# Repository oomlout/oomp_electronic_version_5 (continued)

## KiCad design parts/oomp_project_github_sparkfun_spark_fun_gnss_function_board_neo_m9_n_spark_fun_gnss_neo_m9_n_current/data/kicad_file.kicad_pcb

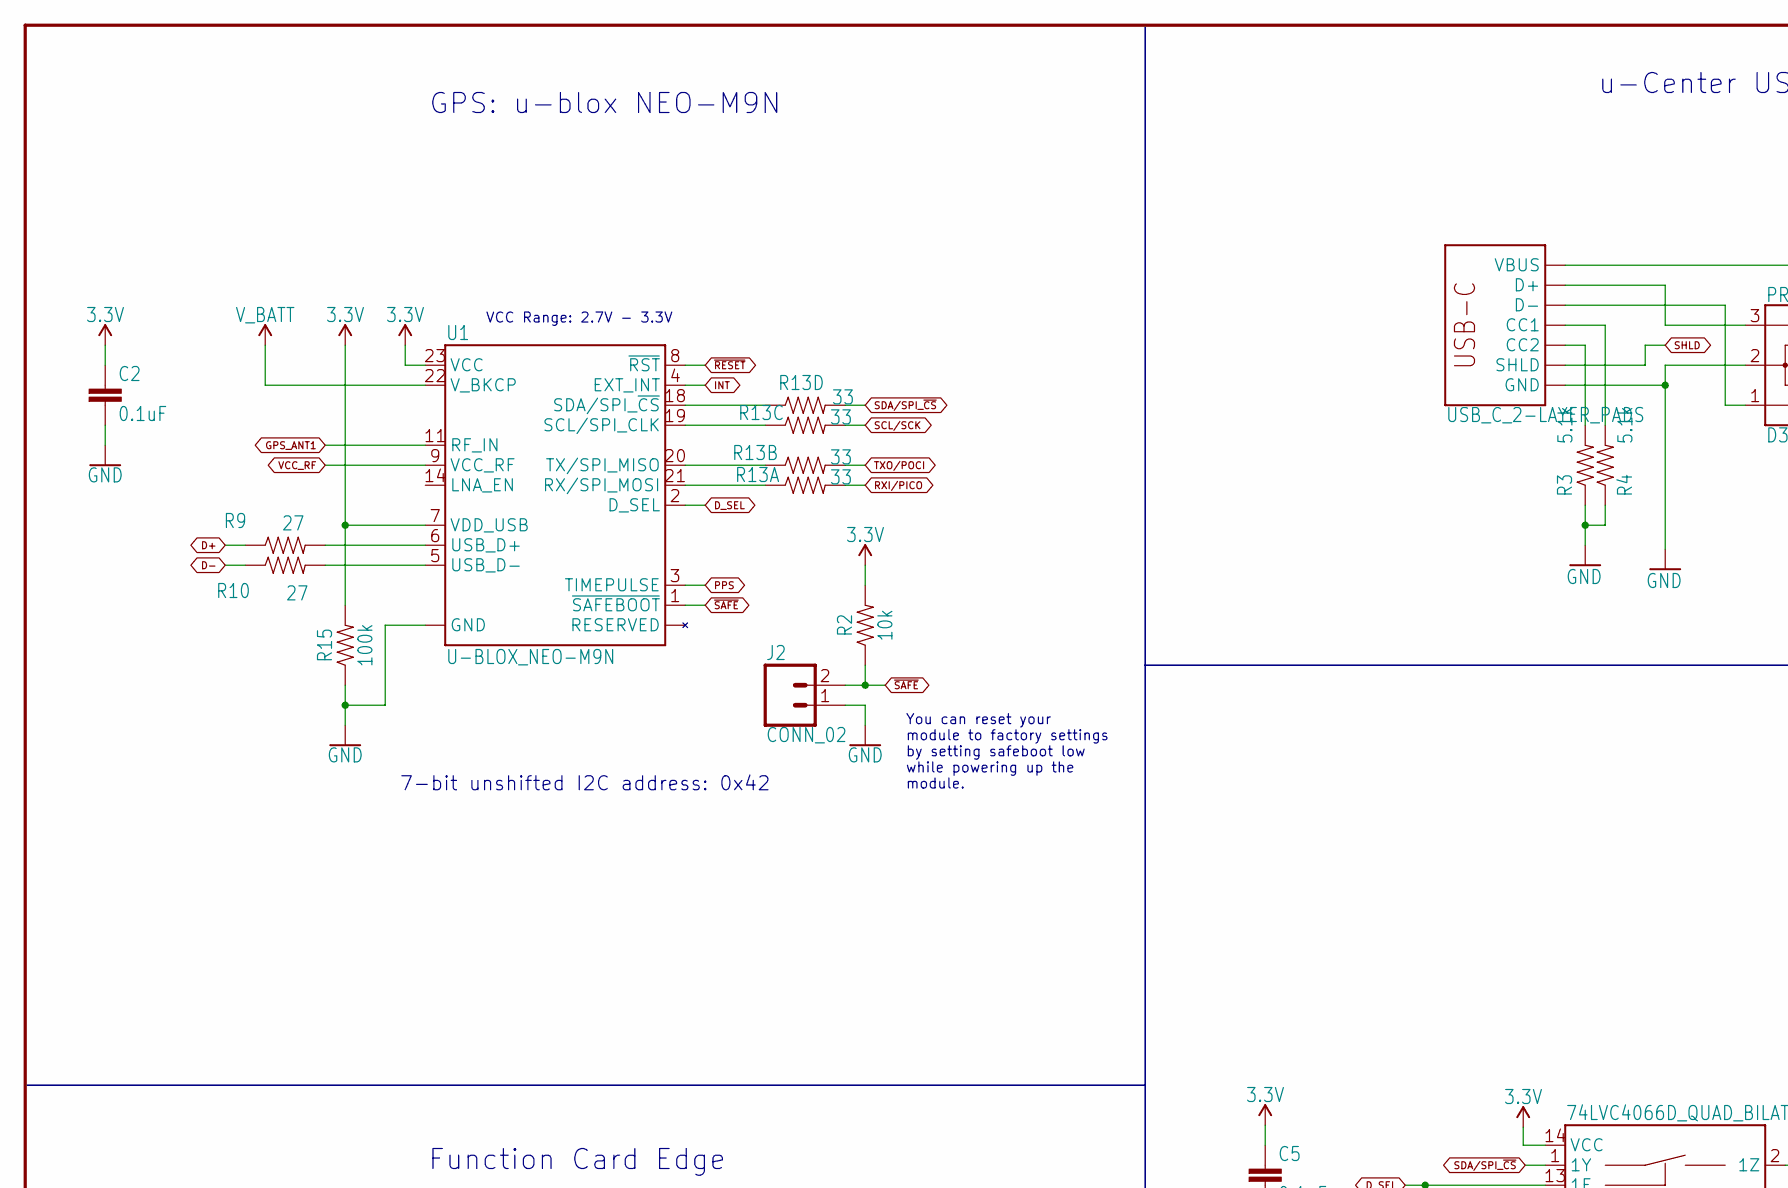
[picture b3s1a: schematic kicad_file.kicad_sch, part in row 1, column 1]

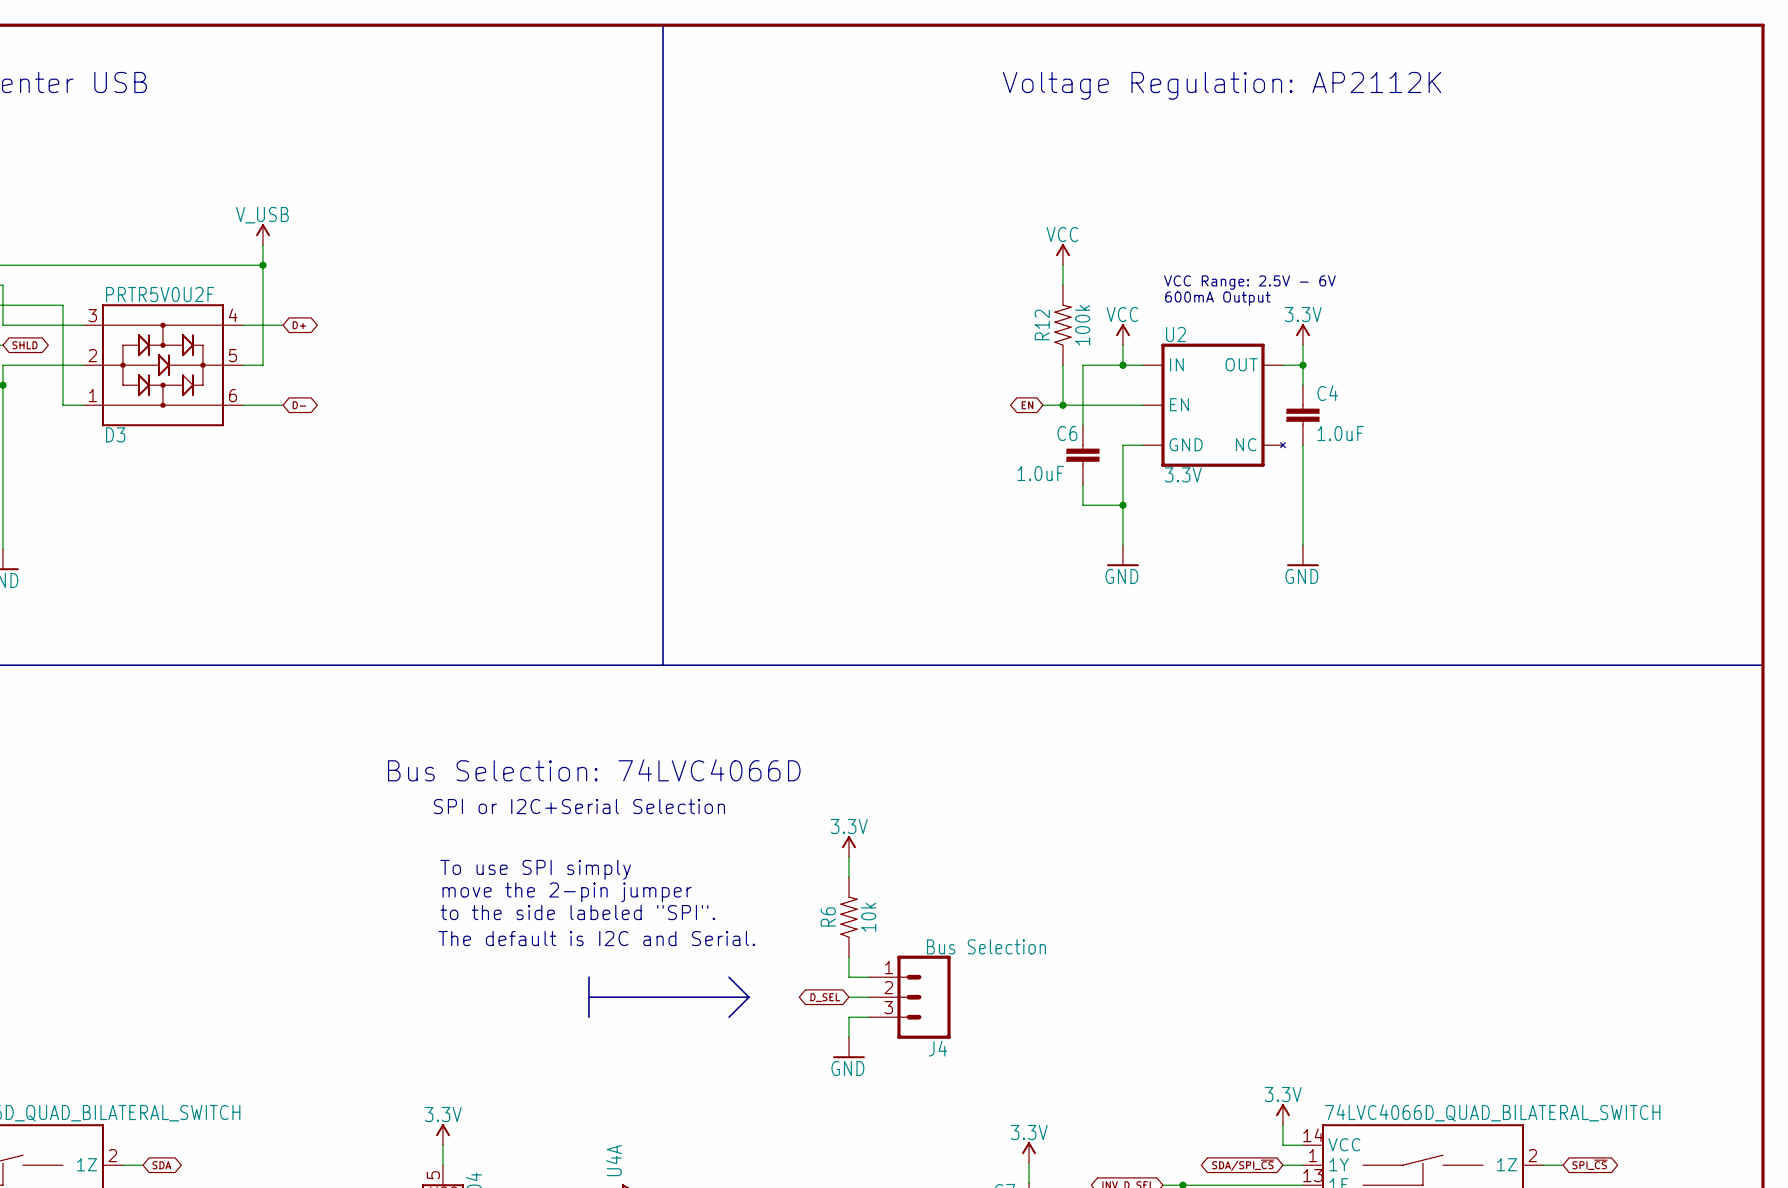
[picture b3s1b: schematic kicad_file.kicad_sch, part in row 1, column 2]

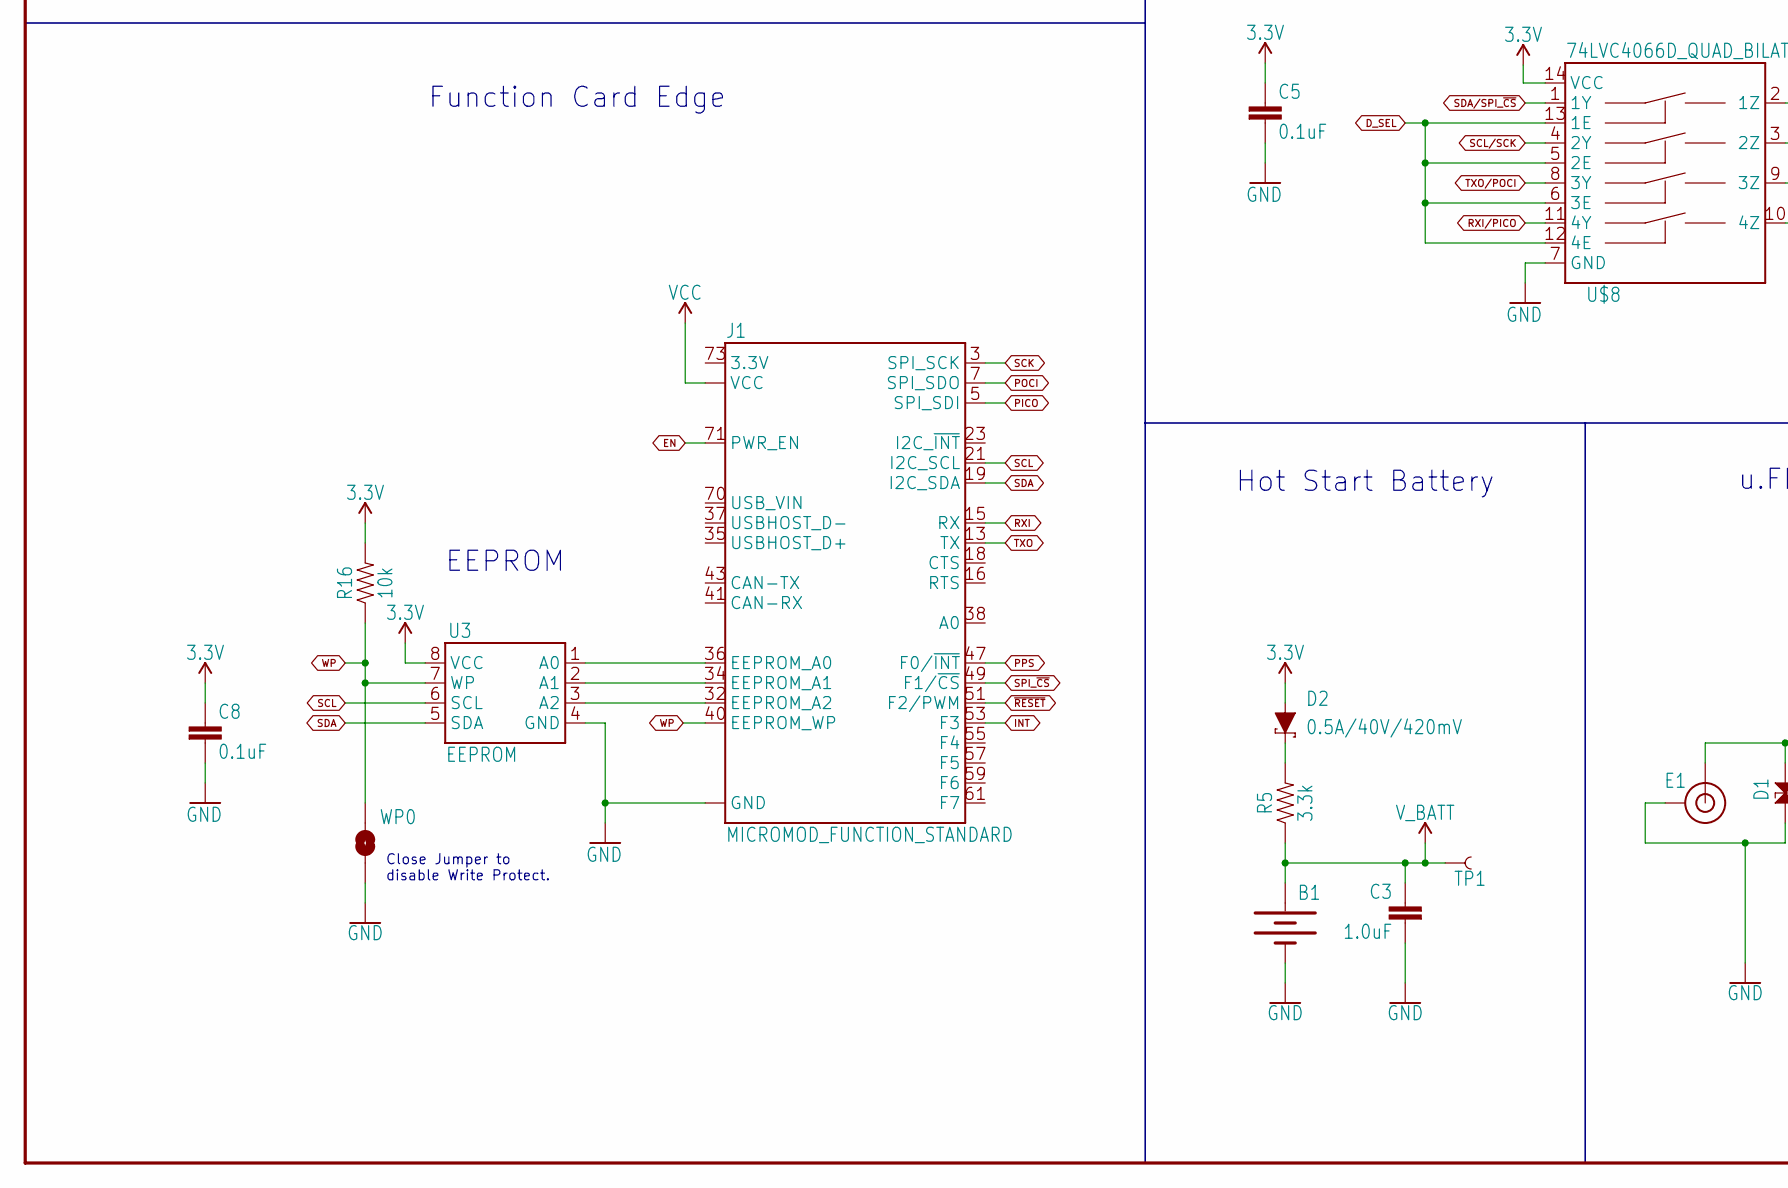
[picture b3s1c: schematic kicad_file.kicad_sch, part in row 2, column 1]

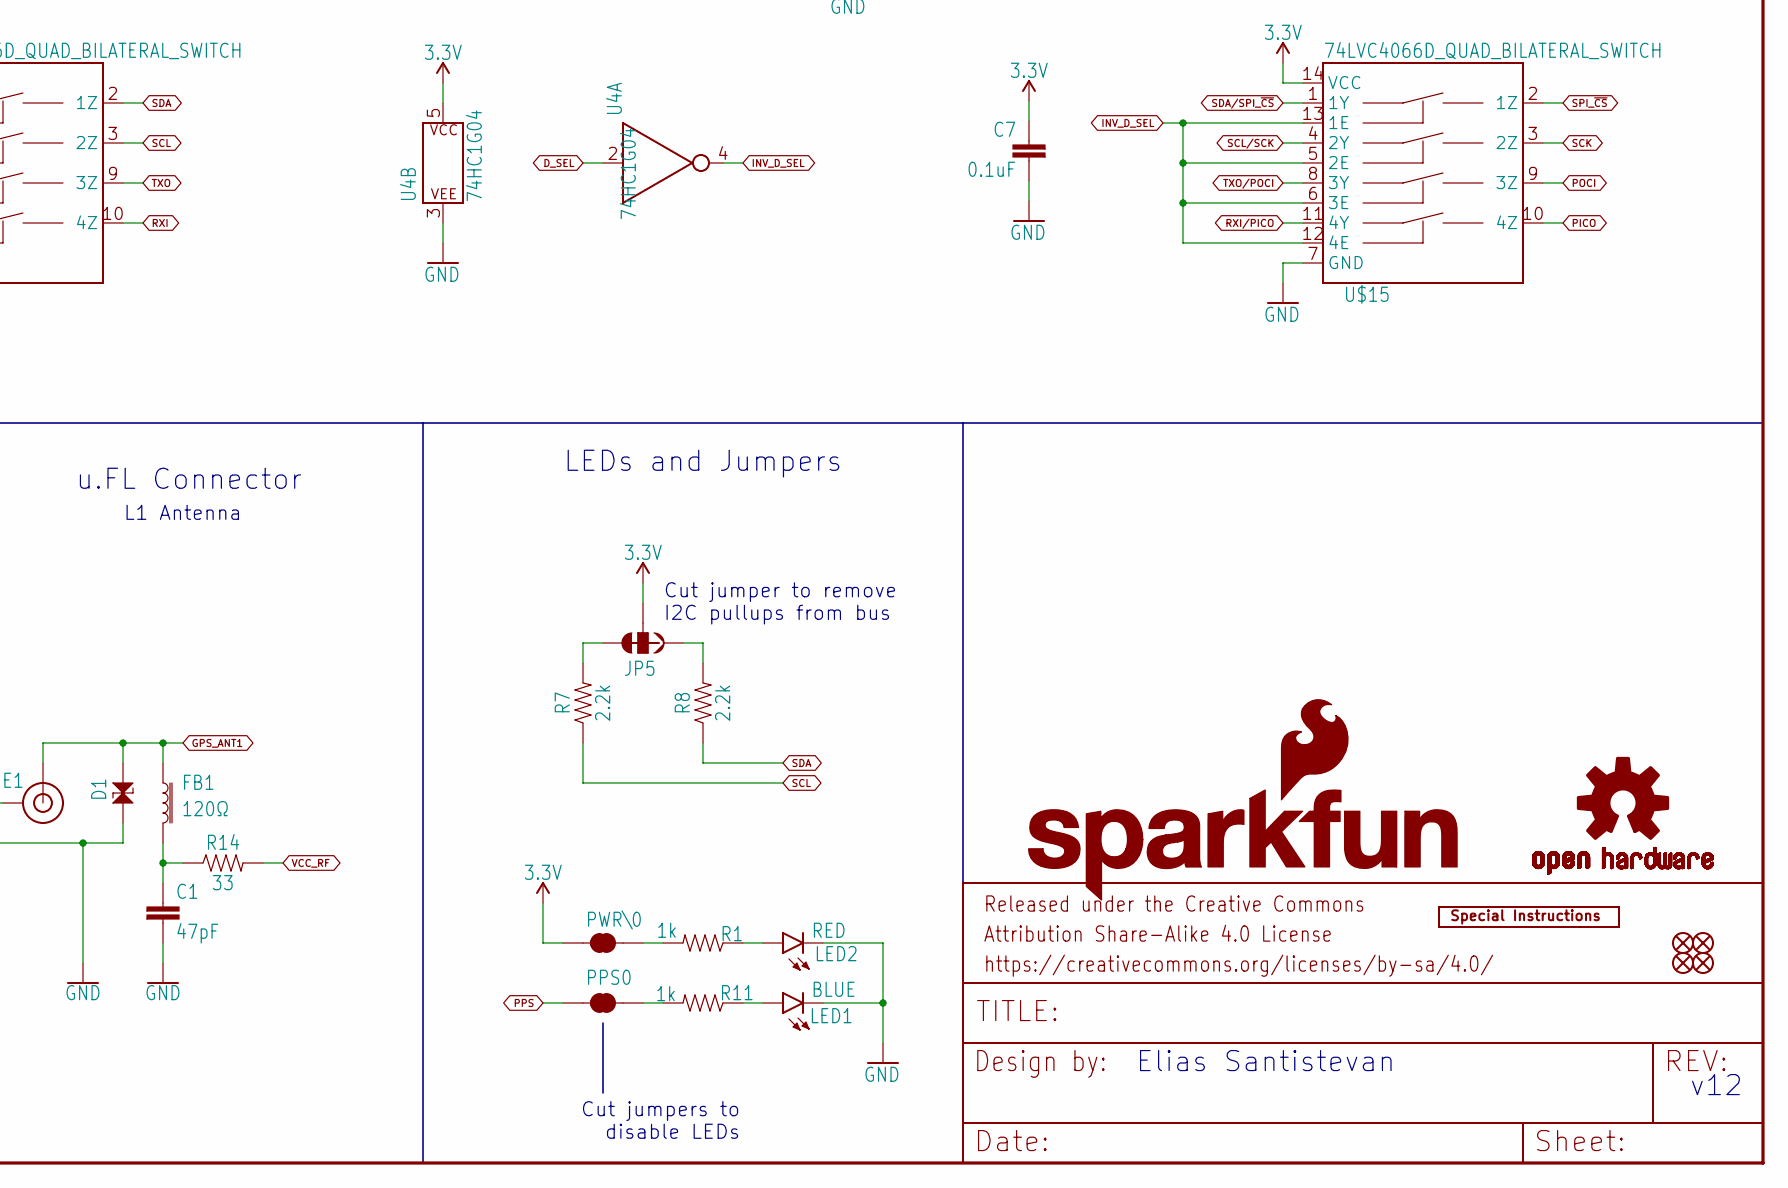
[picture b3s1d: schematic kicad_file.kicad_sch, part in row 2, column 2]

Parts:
B1: 6.8MM_COIN_CELL; MS421R_IV03E
C1: 47pF; 0402
C2: 0.1uF; 0402-TIGHT
C3, C4, C6: 1.0uF; 0603
C5, C7, C8: 0.1uF; 0603
D1: PESD0402-0402T; 0402-TIGHT
D2: 0.5A/40V/420mV; SOD-323
D3: PRTR5V0U2F; SOT886
E1: U.FL
FB1: 120Ω; 0402; MFG_PART BLM15HB121SN1D
FD1, FD2, FD3, FD4: FIDUCIAL1X2; FIDUCIAL-1X2
FRAME2: FRAME-LEDGER; CREATIVE_COMMONS
J1: MICROMOD_FUNCTION_STANDARD; M.2-CARD-E-22_FUNCTION_STANDARD
J2: CONN_02; 1X02
J3: USB_C_2-LAYER_PADS; USB-C-16P-2LAYER-PADS
J4: Bus Selection; 1X03_LOCK
JP5: JUMPER-SMT_3_2-NC_TRACE_SILK; SMT-JUMPER_3_2-NC_TRACE_SILK
LED1: BLUE; LED-0603
LED2: RED; LED-0603
LOGO1: SPECIAL_INSTRUCTIONS-ORDERING; ORDERING_INSTRUCTIONS
LOGO2: SFE_LOGO_NAME_FLAME.2_INCH; SFE_LOGO_NAME_FLAME_.2
LOGO3: OSHW-LOGOS; OSHW-LOGO-S
PPS0: JUMPER-SMT_2_NC_TRACE_SILK; SMT-JUMPER_2_NC_TRACE_SILK
PWR\0: JUMPER-SMT_2_NC_TRACE_SILK; SMT-JUMPER_2_NC_TRACE_SILK
R1, R11: 1k; 0603
R2, R6, R16: 10k; 0603
R3, R4: 5.1k; 0603
R5: 3.3k; 0603
R7, R8: 2.2k; 0603
R9, R10: 27; 0603
R12, R15: 100k; 0603
R13: 33; 1206_RA
R14: 33; 0402
TP1: TEST-POINT3X4; PAD.03X.04
U1: U-BLOX_NEO-M9N; NEO-M9N_M8T_M8U_D9S
U2: 3.3V; SOT23-5
U3: EEPROM; SO08
U4: 74HC1G04; SOT353
U$8, U$15: 74LVC4066D_QUAD_BILATERAL_SWITCH; SO14
WP0: JUMPER-SMT_2_NO_SILK; SMT-JUMPER_2_NO_SILK

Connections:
3.3V: C2.1, C4.1, C5.1, C7.1, C8.1, D2.A, JP5.2, PWR\0.2, R2.2, R6.2, R15.2, R16.2, U1.7 (VDD_USB), U1.23 (VCC), U2.5 (OUT), U3.8 (VCC), U4.5 (P$V+), U$8.14 (VCC), U$15.14 (VCC)
A0: J1.36 (EEPROM_A0), U3.1 (A0)
A1: J1.34 (EEPROM_A1), U3.2 (A1)
A2: J1.32 (EEPROM_A2), U3.3 (A2)
D+: D3.4, R9.1
D-: D3.6, R10.1
D_SEL: J4.2, U1.2 (D_SEL), U4.2 (A), U$8.5 (2E), U$8.6 (3E), U$8.12 (4E), U$8.13 (1E)
EN: J1.71 (PWR_EN), R12.1, U2.3 (EN)
GND: B1.-, C1.2, C2.2, C3.2, C4.2, C5.2, C6.2, C7.2, C8.2, D1.1, D3.2, E1.1 (GND), E1.2 (GND), J1.1 (GND), J1.33 (GND), J1.39 (GND), J1.45 (GND), J1.75 (GND), J1.GND1 (GND), J1.GND2 (GND), J1.GND3 (GND), J1.GND4 (GND), J1.GND5 (GND), J1.GND6 (GND), J2.1, J3.GND, J3.GND2 (GND), J4.3, LED1.C, LED2.C, R3.1, R4.1, R15.1, U1.10 (GND), U1.12 (GND), U1.13 (GND), U1.24 (GND), U2.2 (GND), U3.4 (GND), U4.3 (P$V-), U$8.7 (GND), U$15.7 (GND), WP0.1
GPS_ANT1: D1.2, E1.FEED (SIGNAL), FB1.1, U1.11 (RF_IN)
INT: J1.53 (F3), U1.4 (EXT_INT)
INV_D_SEL: U4.4 (Y), U$15.5 (2E), U$15.6 (3E), U$15.12 (4E), U$15.13 (1E)
unnamed: PWR\0.1, R1.2
unnamed: LED1.A, R11.1
unnamed: C1.1, FB1.2, R14.1
unnamed: PPS0.1, R11.2
unnamed: JP5.1, R8.2
unnamed: D2.C, R5.2
unnamed: J3.A5 (CC1), R4.2
unnamed: JP5.3, R7.2
unnamed: J3.B5 (CC2), R3.2
unnamed: LED2.A, R1.1
unnamed: R9.2, U1.6 (USB_D+)
unnamed: R10.2, U1.5 (USB_D-)
unnamed: J4.1, R6.1
PICO: J1.5 (SPI_SDI), U$15.10 (4Z)
POCI: J1.7 (SPI_SDO), U$15.9 (3Z)
PPS: J1.47 (F0/~INT), PPS0.2, U1.3 (TIMEPULSE)
RXI: J1.15 (RX), U$8.10 (4Z)
RXI/PICO: R13.P8 (2), U$8.11 (4Y), U$15.11 (4Y)
RXLV: R13.P1 (1), U1.21 (RX/SPI_MOSI)
SCK: J1.3 (SPI_SCK), U$15.3 (2Z)
SCL: J1.21 (I2C_SCL), R7.1, U3.6 (SCL), U$8.3 (2Z)
SCL/SCK: R13.P6 (2), U$8.4 (2Y), U$15.4 (2Y)
SCL_LV: R13.P3 (1), U1.19 (SCL/SPI_CLK)
SDA: J1.19 (I2C_SDA), R8.1, U3.5 (SDA), U$8.2 (1Z)
SDA/SPI_~CS: R13.P5 (2), U$8.1 (1Y), U$15.1 (1Y)
SDA_LV: R13.P4 (1), U1.18 (SDA/SPI_~CS)
SHLD: J3.SHLD1 (SHLD), J3.SHLD2 (SHLD), J3.SHLD3 (SHLD), J3.SHLD4 (SHLD)
SPI_~CS: J1.49 (F1/~CS), U$15.2 (1Z)
TXLV: R13.P2 (1), U1.20 (TX/SPI_MISO)
TXO: J1.13 (TX), U$8.9 (3Z)
TXO/POCI: R13.P7 (2), U$8.8 (3Y), U$15.8 (3Y)
USB_D+: D3.3, J3.A6 (D+), J3.B6 (D+)
USB_D-: D3.1, J3.A7 (D-), J3.B7 (D-)
VCC: C6.1, J1.72 (VCC), J1.74 (VCC), R12.2, U2.1 (IN)
VCC_RF: R14.2, U1.9 (VCC_RF)
V_BATT: B1.+, C3.1, R5.1, TP1.1, U1.22 (V_BKCP)
V_USB: D3.5, J3.VBUS1 (VBUS), J3.VBUS2 (VBUS)
WP: J1.40 (EEPROM_WP), R16.1, U3.7 (WP), WP0.2
~RESET: J1.51 (F2/PWM), U1.8 (~RST)
~SAFE: J2.2, R2.1, U1.1 (~SAFEBOOT)

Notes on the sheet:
LEDs and Jumpers
Function Card Edge
Elias Santistevan
Voltage Regulation: AP2112K
VCC Range: 2.7V - 3.3V
Cut jumper to remove I2C pullups from bus
7-bit unshifted I2C address: 0x42
GPS: u-blox NEO-M9N
EEPROM
To use SPI simply move the 2-pin jumper to the side labeled "SPI".
SPI or I2C+Serial Selection
L1 Antenna
Cut jumpers to disable LEDs
v12
u-Center USB
The default is I2C and Serial.
Close Jumper to disable Write Protect.
Bus Selection: 74LVC4066D
VCC Range: 2.5V - 6V 600mA Output
Hot Start Battery
u.FL Connector
You can reset your module to factory settings by setting safeboot low while powering up the module.

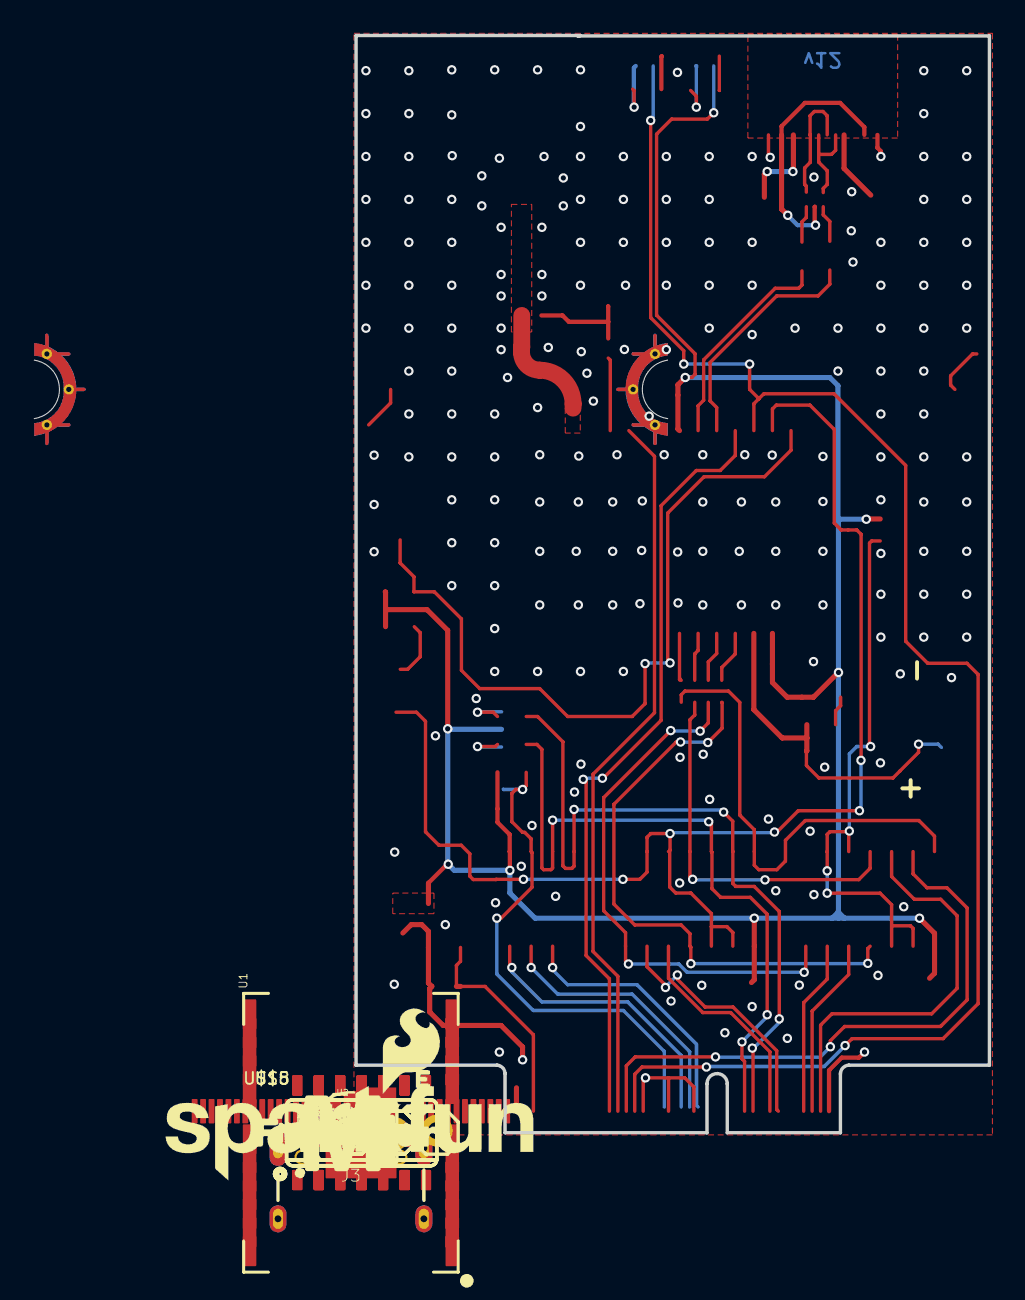
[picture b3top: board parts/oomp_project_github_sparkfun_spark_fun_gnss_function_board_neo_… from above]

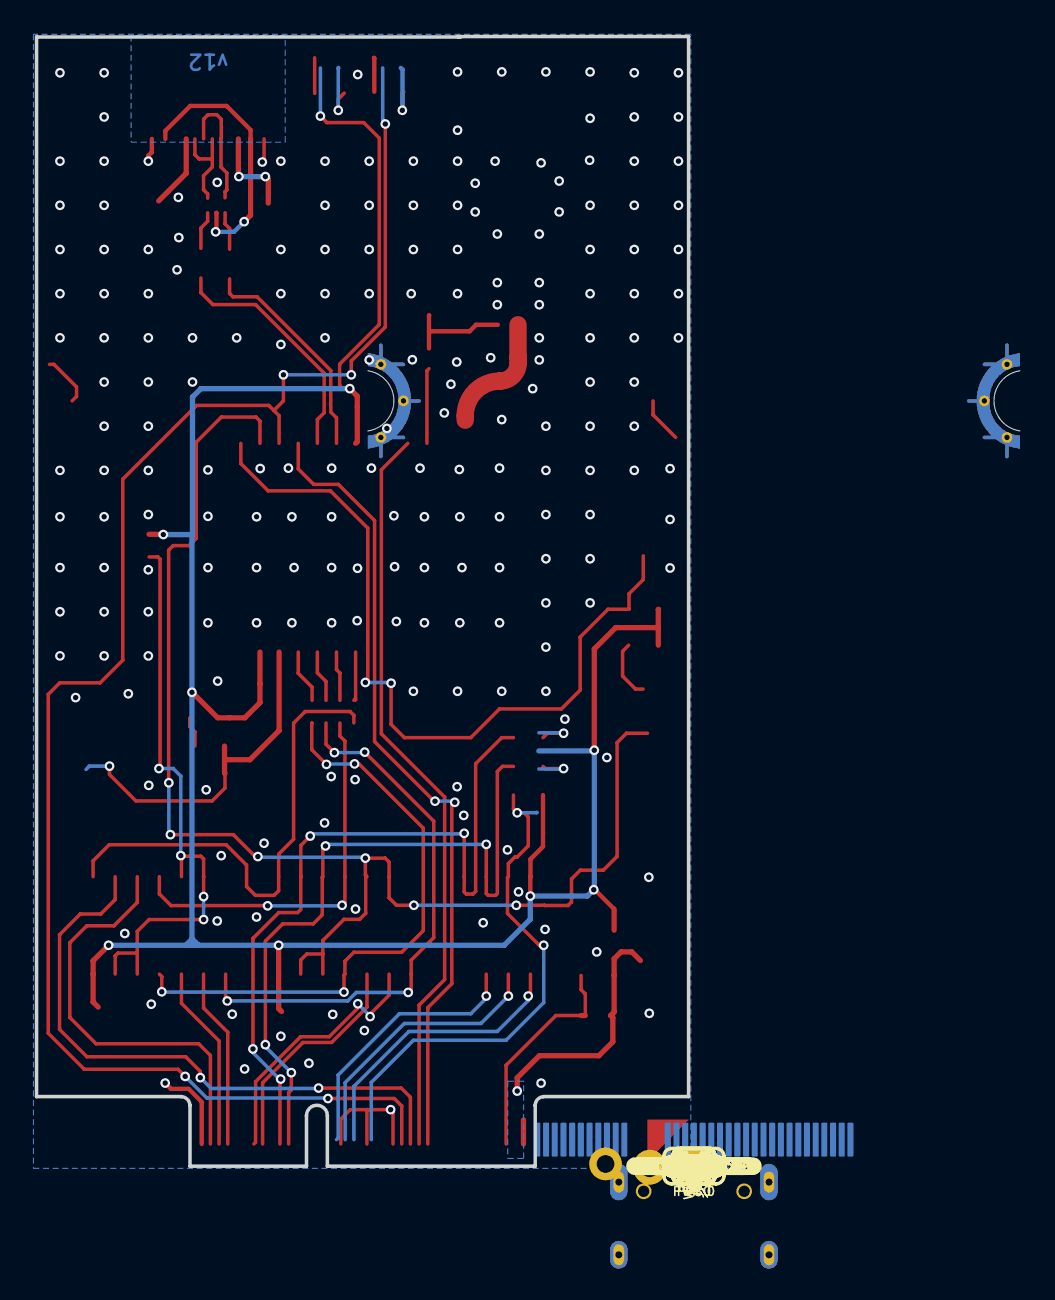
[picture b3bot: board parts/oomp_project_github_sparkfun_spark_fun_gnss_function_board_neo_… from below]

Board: 2 copper layers, 37.5 x 64.9 mm, 79 parts (17 on the bottom side), 52 nets.

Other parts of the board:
U$1: 3V313
U$2: PPS13
U$3: FUNCTION521
U$4, U$23: ##SAFEBOOT##882188213
U$5: U#BLOX11
U$6: NEO#M9N12
U$7: ANTENNA14
U$9: U#CENTER15
U$10: #I2C#18
U$11: MICROMOD_MI_LOGO_1
U$12: #3V3_LED#403132222514
U$13: #PPS_LED#403132222514
U$14: L1321542
U$16, U$24: #SPI#40313521
U$17, U$26: #SERIAL#I2C#40313523
U$18, U$22: #BUS_SELECT#509
U$19, U$25: #DSEL#40313522
U$20: #WP#13215403132222564
U$21: GNSS2222502

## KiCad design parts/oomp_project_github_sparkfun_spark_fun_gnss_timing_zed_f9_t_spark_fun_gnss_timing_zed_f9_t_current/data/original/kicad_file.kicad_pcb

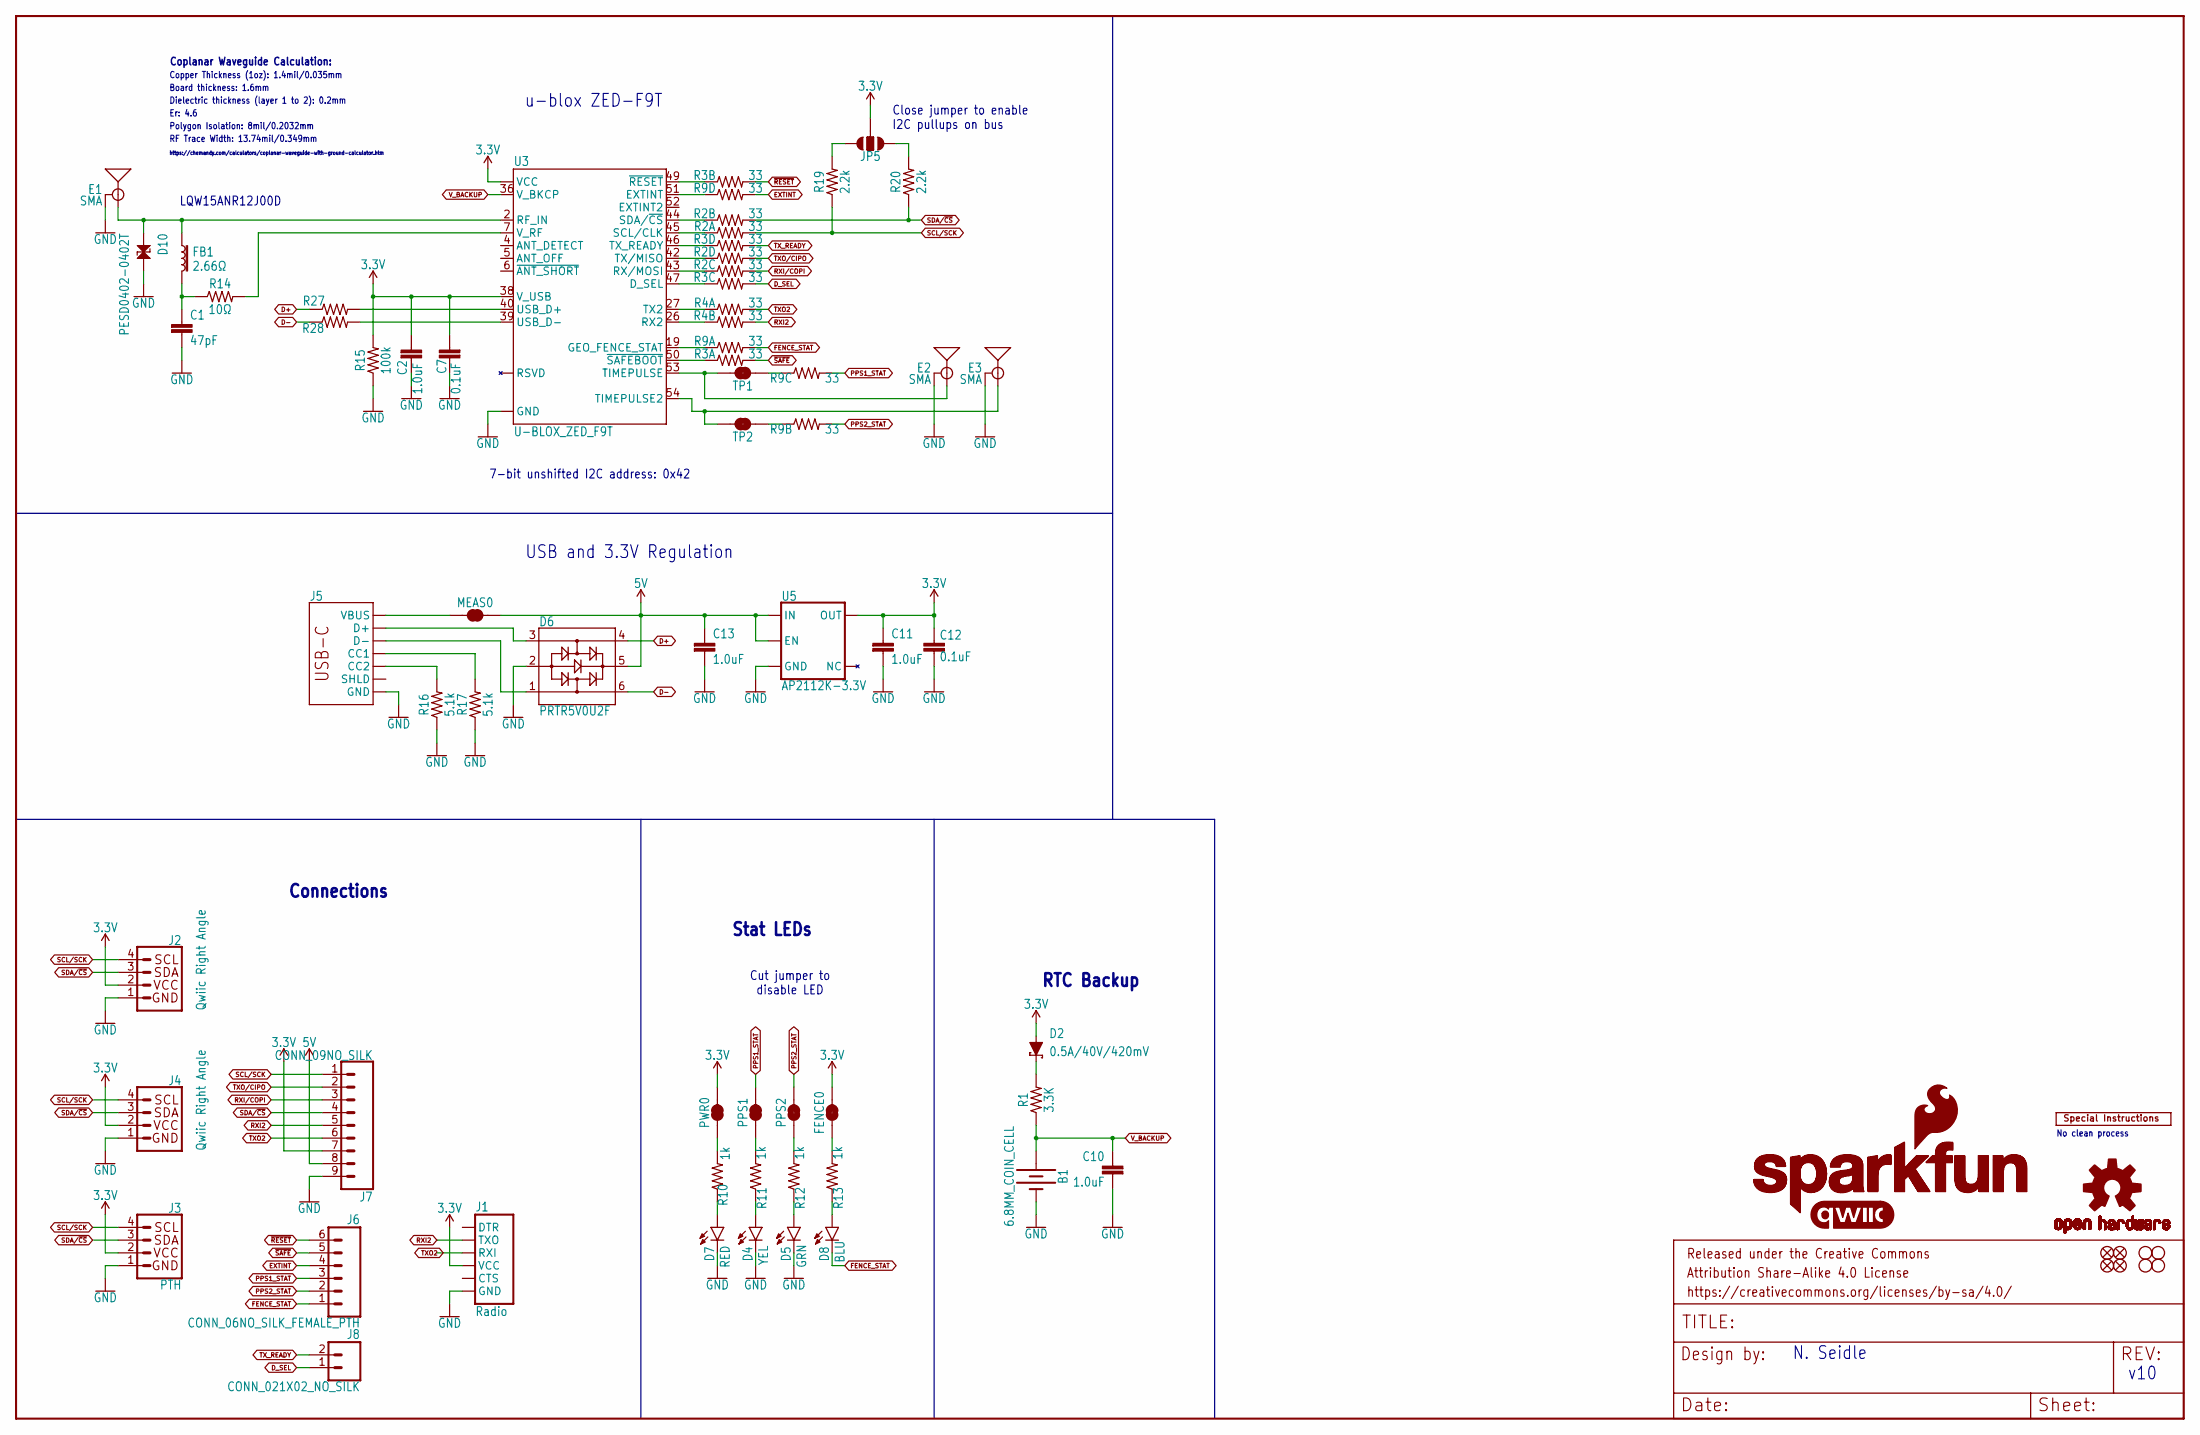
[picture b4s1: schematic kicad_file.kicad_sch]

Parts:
B1: 6.8MM_COIN_CELL; ML414H_IV01E
C1: 47pF; 0402-TIGHT
C2, C10, C11, C13: 1.0uF; 0402-TIGHT
C7, C12: 0.1uF; 0402-TIGHT
D2: 0.5A/40V/420mV; SOD-323
D4: YEL; LED-0603
D5: GRN; LED-0603
D6: PRTR5V0U2F; SOT886
D7: RED; LED-0603
D8: BLU; LED-0603
D10: PESD0402-0402T; 0402-TIGHT
E1, E2, E3: SMA; SMA-EDGE
FB1: 2.66Ω; 0402-TIGHT
FENCE0: JUMPER-SMT_2_NC_TRACE_SILK; SMT-JUMPER_2_NC_TRACE_SILK
FRAME2: FRAME-LEDGER; CREATIVE_COMMONS
H1, H2, H3, H4: STAND-OFF
J1: Radio; 1X06_NO_SILK
J2, J4: Qwiic Right Angle; JST04_1MM_RA
J3: PTH; 1X04_NO_SILK
J5: USB Female Type C Connector; USB-C-16P_4LAYER-PADS
J6: CONN_06NO_SILK_FEMALE_PTH; 1X06_NO_SILK
J7: CONN_09NO_SILK; 1X09_NO_SILK
J8: CONN_021X02_NO_SILK; 1X02_NO_SILK
JP5: JUMPER-SMT_3_NO_SILK; SMT-JUMPER_3_NO_SILK
JP21, JP61, JP71, JP81: FIDUCIALUFIDUCIAL; FIDUCIAL-MICRO
LOGO1: OSHW-LOGOMINI; OSHW-LOGO-MINI
LOGO2: SFE_LOGO_NAME_FLAME.1_INCH; SFE_LOGO_NAME_FLAME_.1
LOGO4: QWIIC_LOGO_4MM; QWIIC_4MM
LOGO5: SFE_LOGO_NAME.1_INCH; SFE_LOGO_NAME_.1
MEAS0: JUMPER-COMBO_2_NC_TRACE; COMBO-JUMPER_2_NC_TRACE
PPS1, PPS2: JUMPER-SMT_2_NC_TRACE_SILK; SMT-JUMPER_2_NC_TRACE_SILK
PWR0: JUMPER-SMT_2_NC_TRACE_SILK; SMT-JUMPER_2_NC_TRACE_SILK
R1: 3.3K; 0402-TIGHT
R2, R3, R4, R9: 33; 1206_RA
R10, R11, R12, R13: 1k; 0402-TIGHT
R14: 10Ω; 0402-TIGHT
R15: 100k; 0402-TIGHT
R16, R17: 5.1k; 0402-TIGHT
R19, R20: 2.2k; 0402-TIGHT
R27, R28: 27OHM; 0402-TIGHT
TP1, TP2: JUMPER-SMT_2_NC_TRACE_SILK; SMT-JUMPER_2_NC_TRACE_SILK
U3: U-BLOX_ZED_F9T; ZED-F9X
U5: AP2112K-3.3V; SOT23-5
U$2: SPECIAL_INSTRUCTIONS-ORDERING; ORDERING_INSTRUCTIONS

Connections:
3.3V: C2.1, C7.2, C11.1, C12.2, D2.A, FENCE0.2, J1.4 (VCC), J2.2, J3.2 (VCC), J4.2, J7.7, JP5.2, PWR0.2, R15.2, U3.33 (VCC), U3.34 (VCC), U3.38 (V_USB), U5.5 (OUT)
5V: C13.1, D6.5, J7.8, MEAS0.2, MEAS0.4 (2), U5.1 (IN), U5.3 (EN)
ANT_VCC: C1.1, FB1.2, R14.1
CC1: J5.A5 (CC1), R17.2
CC2: J5.B5 (CC2), R16.2
D+: D6.4, R27.1
D-: D6.6, R28.1
DSEL_LV: R3.P3 (1), U3.47 (D_SEL)
D_SEL: J8.1, R3.P6 (2)
EXTINT: J6.4, R9.P5 (2)
EXTINT_LV: R9.P4 (1), U3.51 (EXTINT)
FENCE_LV: R9.P1 (1), U3.19 (GEO_FENCE_STAT)
FENCE_STAT: D8.C, J6.1, R9.P8 (2)
GND: B1.-, C1.2, C2.2, C7.1, C10.2, C11.2, C12.1, C13.2, D4.C, D5.C, D6.2, D7.C, D10.2, E1.GND@0 (GND), E1.GND@1 (GND), E1.GND@2 (GND), E1.GND@3 (GND), E2.GND@0 (GND), E2.GND@1 (GND), E2.GND@2 (GND), E2.GND@3 (GND), E3.GND@0 (GND), E3.GND@1 (GND), E3.GND@2 (GND), E3.GND@3 (GND), J1.6 (GND), J2.1, J3.1 (GND), J4.1, J5.GND, J5.GND2 (GND), J7.9, R15.1, R16.1, R17.1, U3.1 (GND), U3.3 (GND), U3.12 (GND), U3.14 (GND), U3.32 (GND), U3.37 (GND), U3.41 (GND), U3.48 (GND), U3.G1 (GND), U3.G2 (GND), U3.G3 (GND), U3.G4 (GND), U3.G5 (GND), U3.G6 (GND), U3.G7 (GND), U3.G8 (GND), U3.G9 (GND), U3.G10 (GND), U3.G11 (GND), U3.G12 (GND), U3.G13 (GND), U3.G14 (GND), U3.G15 (GND), U3.G16 (GND), U3.G17 (GND), U3.G18 (GND), U3.G19 (GND), U3.G20 (GND), U3.G21 (GND), U3.G22 (GND), U3.G23 (GND), U3.G24 (GND), U3.G25 (GND), U3.G26 (GND), U3.G27 (GND), U3.G28 (GND), U3.G29 (GND), U3.G30 (GND), U3.G31 (GND), U3.G32 (GND), U3.G33 (GND), U3.G34 (GND), U3.G35 (GND), U3.G36 (GND), U3.G37 (GND), U3.G38 (GND), U3.G39 (GND), U3.G40 (GND), U3.G41 (GND), U3.G42 (GND), U3.G43 (GND), U3.G44 (GND), U3.G45 (GND), U3.G46 (GND), U3.G47 (GND), U3.G48 (GND), U5.2 (GND)
GPS_ANT1: D10.1, E1.SIG (SIGNAL), FB1.1, U3.2 (RF_IN)
unnamed: D4.A, R11.1
unnamed: PPS1.1, R11.2
unnamed: J5.VBUS1 (VBUS), J5.VBUS2 (VBUS), MEAS0.1, MEAS0.3 (1)
unnamed: R9.P3 (1), TP1.1
unnamed: D2.C, R1.2
unnamed: R9.P2 (1), TP2.1
unnamed: R27.2, U3.40 (USB_D+)
unnamed: R28.2, U3.39 (USB_D-)
unnamed: R14.2, U3.7 (V_RF)
unnamed: D7.A, R10.1
unnamed: D5.A, R12.1
unnamed: PPS2.1, R12.2
unnamed: D8.A, R13.1
unnamed: FENCE0.1, R13.2
unnamed: PWR0.1, R10.2
unnamed: JP5.1, R20.2
unnamed: JP5.3, R19.2
PPS1_STAT: J6.3, PPS1.2, R9.P6 (2)
PPS2_STAT: J6.2, PPS2.2, R9.P7 (2)
RX1_LV: R2.P3 (1), U3.43 (RX/MOSI)
RX2_LV: R4.P2 (1), U3.26 (RX2)
RXI2: J1.3 (TXO), J7.5, R4.P7 (2)
RXI/COPI: J7.3, R2.P6 (2)
SCL/SCK: J2.4, J3.4 (SCL), J4.4, J7.1, R2.P8 (2), R19.1
SCL_LV: R2.P1 (1), U3.45 (SCL/CLK)
SDA/~CS: J2.3, J3.3 (SDA), J4.3, J7.4, R2.P7 (2), R20.1
SDA_LV: R2.P2 (1), U3.44 (SDA/~CS)
TP1_LV: E2.SIG (SIGNAL), TP1.2, U3.53 (TIMEPULSE)
TP2_LV: E3.SIG (SIGNAL), TP2.2, U3.54 (TIMEPULSE2)
TX1_LV: R2.P4 (1), U3.42 (TX/MISO)
TX2_LV: R4.P1 (1), U3.27 (TX2)
TXO2: J1.2 (RXI), J7.6, R4.P8 (2)
TXO/CIPO: J7.2, R2.P5 (2)
TX_READY: J8.2, R3.P5 (2)
TX_READY_LV: R3.P4 (1), U3.46 (TX_READY)
UNP_D+: D6.3, J5.A6 (D+), J5.B6 (D+)
UNP_D-: D6.1, J5.A7 (D-), J5.B7 (D-)
V_BACKUP: B1.+, C10.1, R1.1, U3.36 (V_BKCP)
~RESET: J6.6, R3.P7 (2)
~RESET_LV: R3.P2 (1), U3.49 (~RESET)
~SAFE: J6.5, R3.P8 (2)
~SAFE_LV: R3.P1 (1), U3.50 (~SAFEBOOT)

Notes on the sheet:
https://chemandy.com/calculators/coplanar-waveguide-with-ground-calculator.htm
LQW15ANR12J00D
Coplanar Waveguide Calculation:
RTC Backup
USB and 3.3V Regulation
Dielectric thickness (layer 1 to 2): 0.2mm
Board thickness: 1.6mm
u-blox ZED-F9T
Cut jumper to disable LED
Connections
Close jumper to enable I2C pullups on bus
No clean process
7-bit unshifted I2C address: 0x42
N. Seidle
RF Trace Width: 13.74mil/0.349mm
Copper Thickness (1oz): 1.4mil/0.035mm
Polygon Isolation: 8mil/0.2032mm
Er: 4.6
Stat LEDs
v10

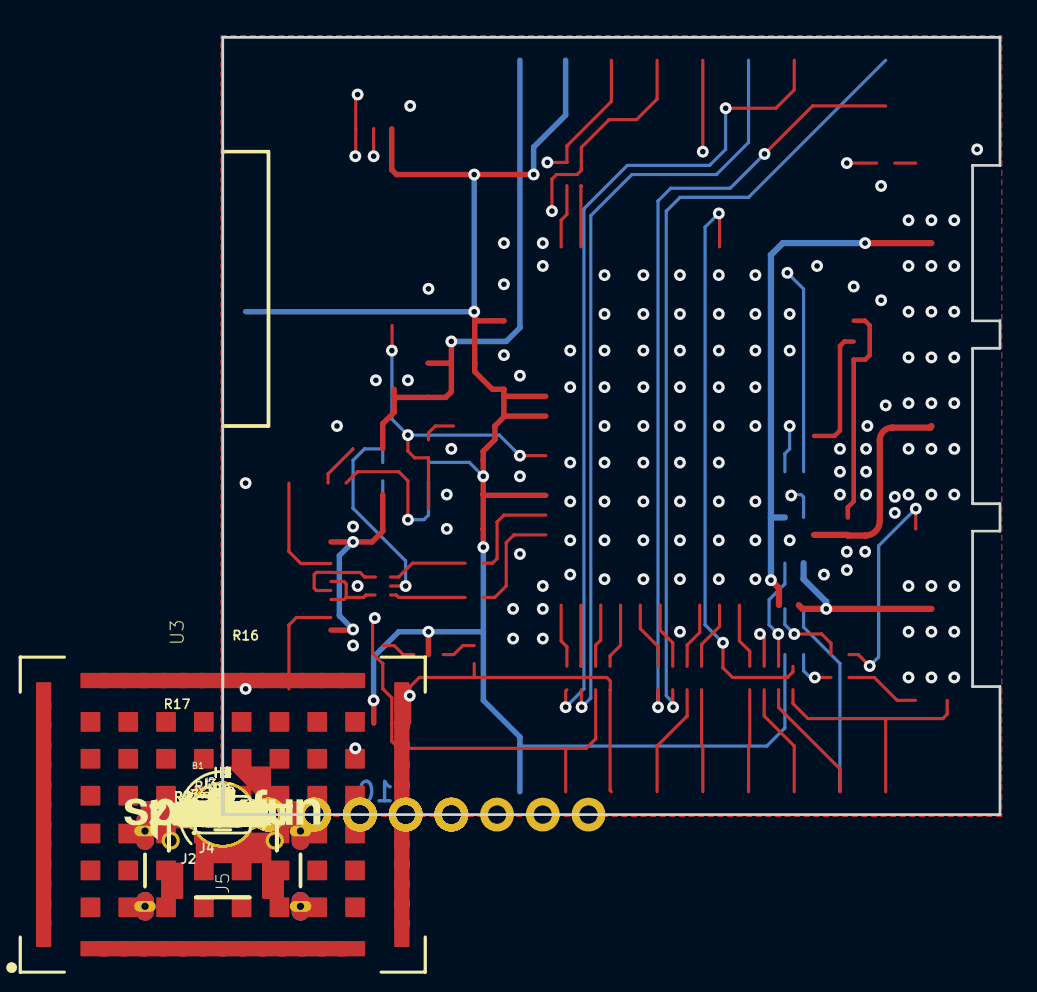
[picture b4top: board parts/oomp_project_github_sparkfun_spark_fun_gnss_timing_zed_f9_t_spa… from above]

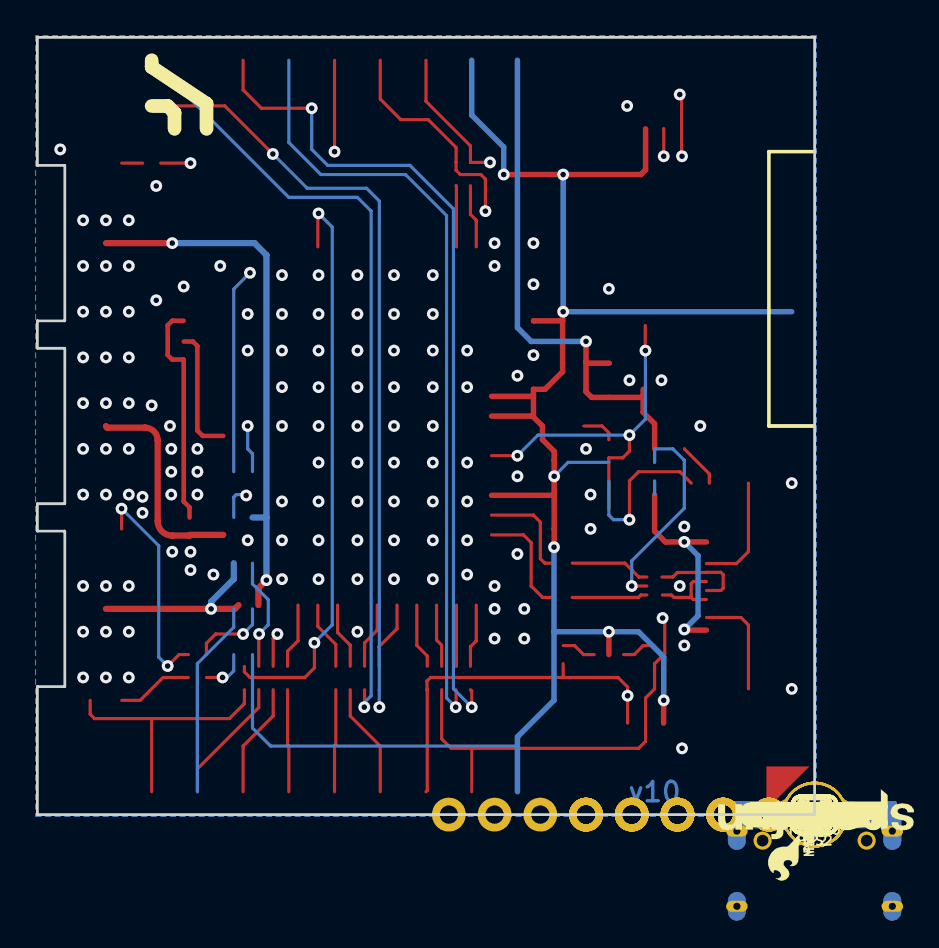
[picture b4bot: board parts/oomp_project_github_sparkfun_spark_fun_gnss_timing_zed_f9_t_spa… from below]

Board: 4 copper layers, 43.2 x 43.2 mm, 146 parts (47 on the bottom side), 57 nets.

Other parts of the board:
LOGO3: QWIIC_LOGO_4MM; QWIIC_4MM
U$1, U$29, U$35, U$36, U$59, U$60: #3#3V#0
U$3, U$28: #5V#1
U$4, U$27, U$38, U$39, U$61, U$62: #GND#2
U$5, U$8: ##CS##4
U$6: L1#L20
U$7, U$21: TIME0
U$9, U$10: #CIPO#6
U$11, U$12: #COPI#5
U$13: ACTIVE1
U$14, U$16: #RX2#1
U$15, U$37: ##RST##0
U$17, U$53: #SCL#3
U$18, U$22: #SDA#2
U$19, U$25: PULSE1
U$20: 12
U$23, U$24: #TX2#0
U$26: 20
U$30: #SCK#5
U$31: ANT1
U$32: #_TX2#0
U$33: #D_SEL#1
U$34, U$77: ZED#F9T0
U$40, U$70: GNSS0
U$41: ##SAFE##1
U$42, U$43: #INT#2
U$44, U$65: #FENCE#0
U$45: #TP2_LED#0
U$46, U$47: #TP1#3
U$48, U$49: #TP2#4
U$50: #TP2#0
U$51: #_FENCE#0
U$52: #TP1#0
U$54: #TP1_LED#0
U$55: #_RX2#0
U$56: PWR0
U$57: #PWR#0
U$58: #RX2_#0
U$63: TP10
U$64: TP21
U$66: #TX2_#0
U$67: #TX_RDY#0
U$68: #MEAS#0
U$69: #I�C#0
U$71, U$74: TIME1
U$72: ##SAFE##0
U$73: RTCM0
U$75: CORRECTION1
U$76: RTCM_0
U$78: FEN0
